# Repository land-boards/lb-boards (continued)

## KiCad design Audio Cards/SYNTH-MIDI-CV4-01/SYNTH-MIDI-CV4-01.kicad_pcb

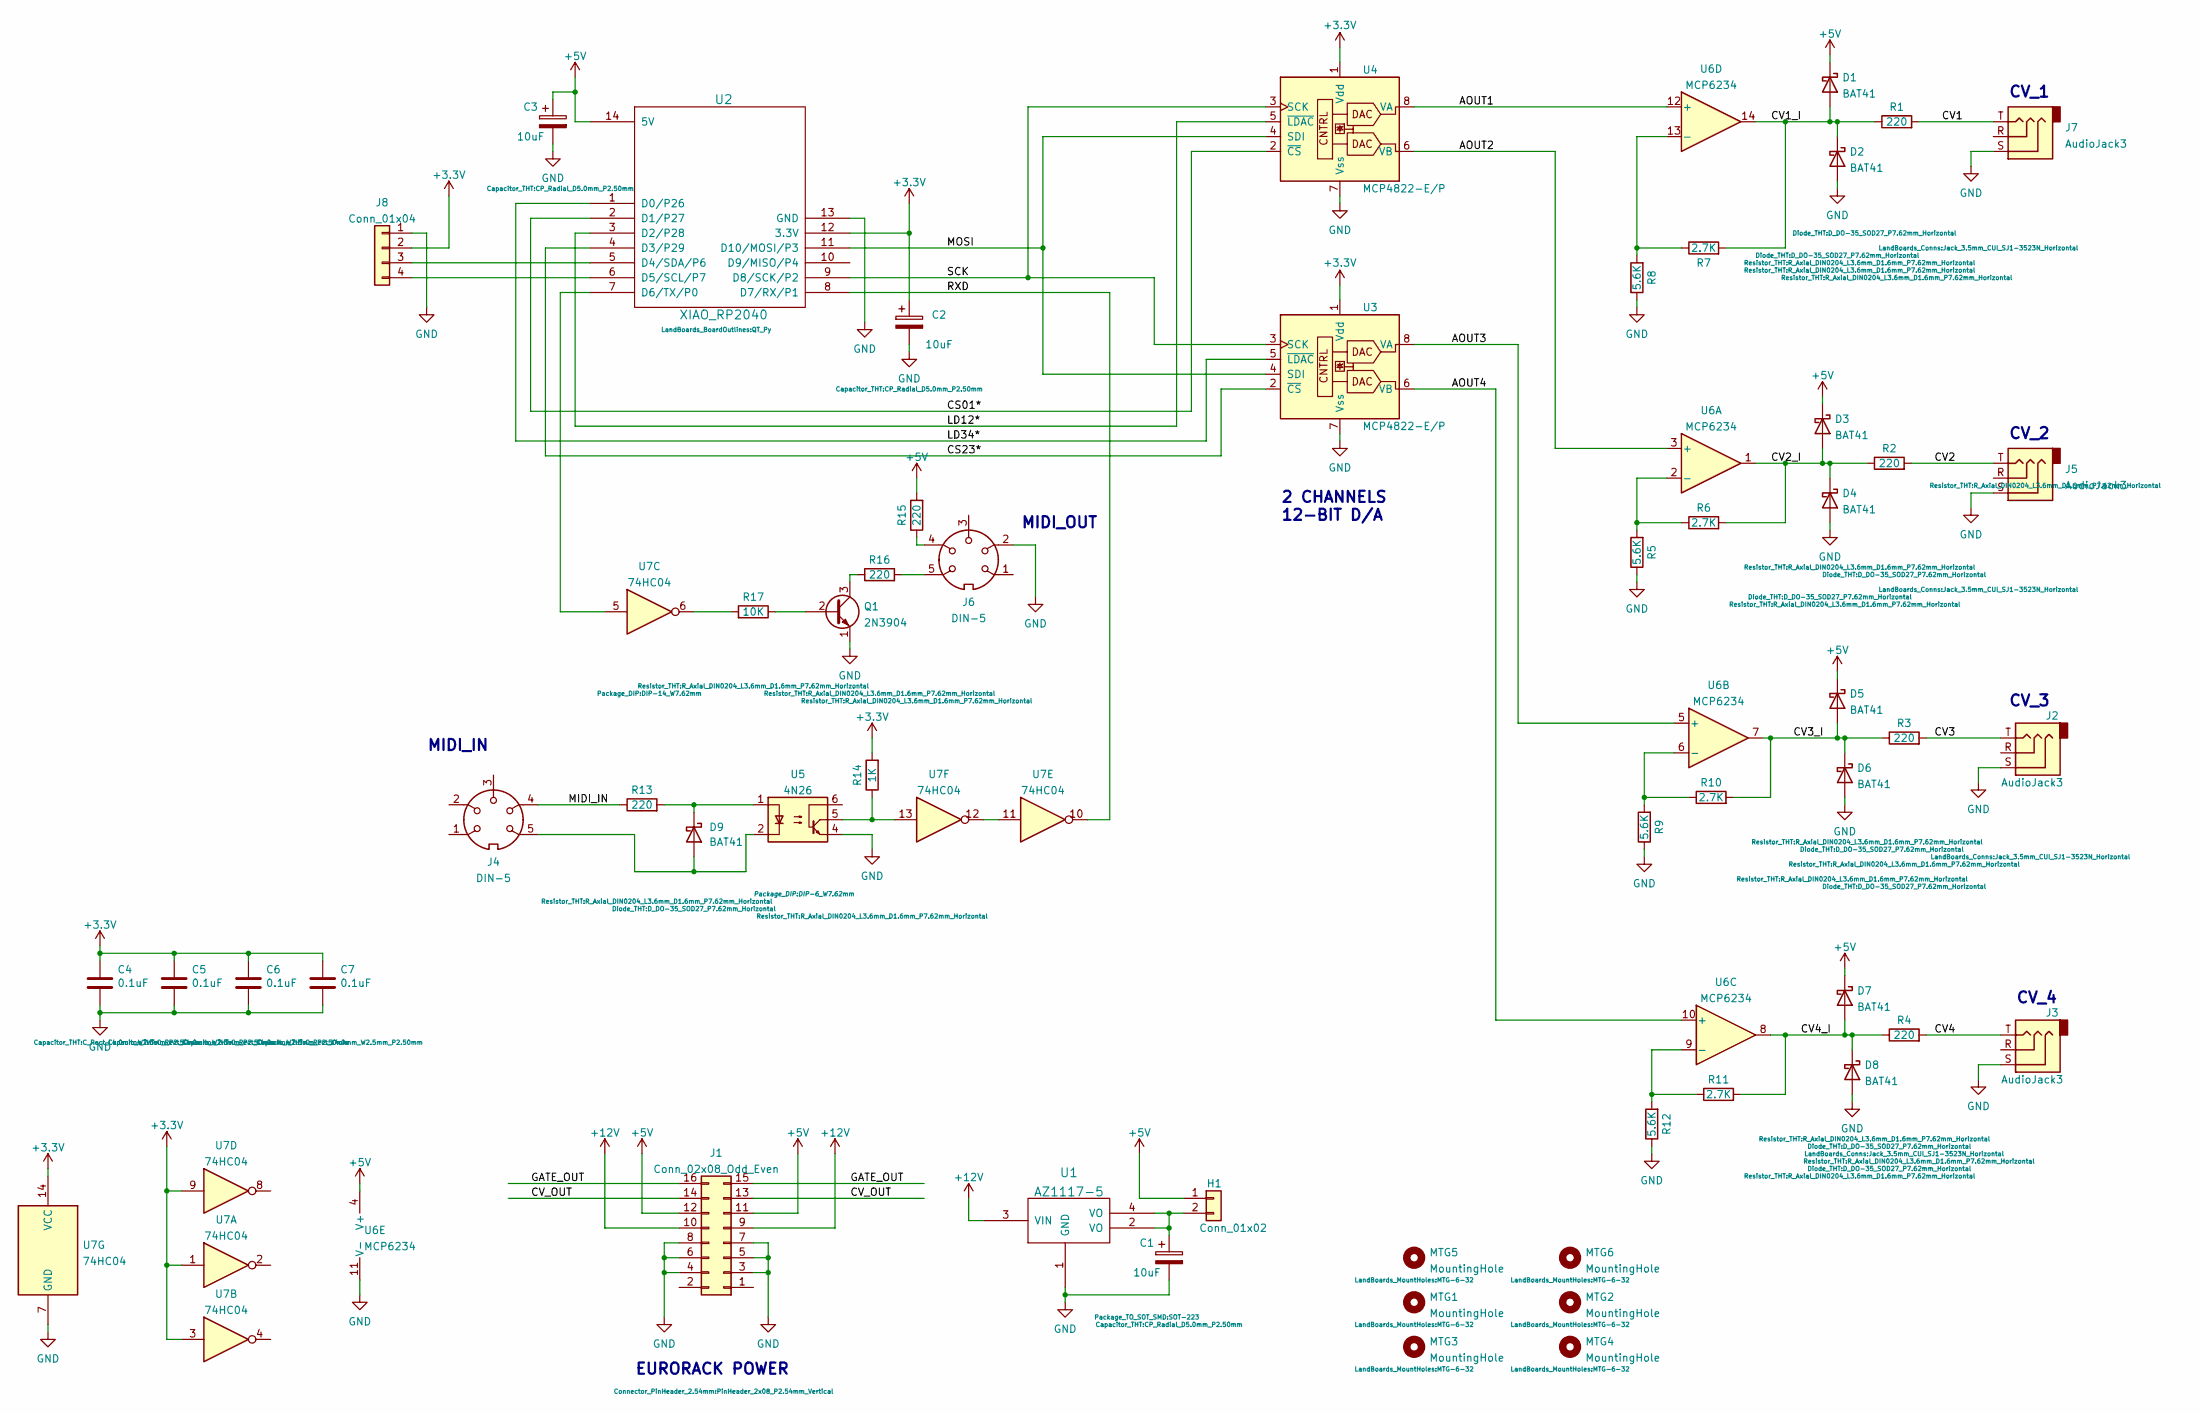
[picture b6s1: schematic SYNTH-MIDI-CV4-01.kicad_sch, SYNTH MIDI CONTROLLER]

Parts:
C1, C2, C3: 10uF; CP_Radial_D5.0mm_P2.50mm
C4, C5, C6, C7: 0.1uF; C_Rect_L4.0mm_W2.5mm_P2.50mm
D1, D2, D3, D4, D5, D6, D7, D8, D9: BAT41; D_DO-35_SOD27_P7.62mm_Horizontal
H1: Conn_01x02; PinHeader_1x02_P2.54mm_Vertical
J1: Conn_02x08_Odd_Even; PinHeader_2x08_P2.54mm_Vertical
J2, J3, J5, J7: AudioJack3; Jack_3.5mm_CUI_SJ1-3523N_Horizontal
J4, J6: DIN-5; MIDI_DIN-5
J8: Conn_01x04
MTG1, MTG2, MTG3, MTG4, MTG5, MTG6: MountingHole; MTG-6-32
Q1: 2N3904; TO-92_Inline
R1, R2, R3, R4, R13, R15, R16: 220; R_Axial_DIN0204_L3.6mm_D1.6mm_P7.62mm_Horizontal
R5, R8, R9, R12: 5.6K; R_Axial_DIN0204_L3.6mm_D1.6mm_P7.62mm_Horizontal
R6, R7, R10, R11: 2.7K; R_Axial_DIN0204_L3.6mm_D1.6mm_P7.62mm_Horizontal
R14: 1K; R_Axial_DIN0204_L3.6mm_D1.6mm_P7.62mm_Horizontal
R17: 10K; R_Axial_DIN0204_L3.6mm_D1.6mm_P7.62mm_Horizontal
U1: AZ1117-5; SOT-223
U2: XIAO_RP2040; QT_Py
U3, U4: MCP4822-E/P; DIP-8_W7.62mm
U5: 4N26; DIP-6_W7.62mm
U6: MCP6234; DIP-14_W7.62mm
U7: 74HC04

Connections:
+3V3: C2.1, C4.1, C5.1, C6.1, C7.1, J8.2, R14.2, U2.12 (3.3V), U3.1 (Vdd), U4.1 (Vdd), U7.1, U7.3, U7.9, U7.14 (VCC)
+5V: C3.1, D1.1 (K), D3.1 (K), D5.1 (K), D7.1 (K), H1.1, J1.11, J1.12, R15.2, U2.14 (5V), U6.4 (V+)
+12V: J1.9, J1.10, U1.3 (VIN)
/AOUT1: U4.8 (VA), U6.12 (+)
/AOUT2: U4.6 (VB), U6.3 (+)
/AOUT3: U3.8 (VA), U6.5 (+)
/AOUT4: U3.6 (VB), U6.10 (+)
/CS01*: U2.2 (D1/P27), U4.2 (~CS)
/CS23*: U2.4 (D3/P29), U3.2 (~CS)
/CV1: J7.T, R1.2
/CV1_I: D1.2 (A), D2.1 (K), R1.1, R7.2, U6.14
/CV2: J5.T, R2.2
/CV2_I: D3.2 (A), D4.1 (K), R2.1, R6.2, U6.1
/CV3: J2.T, R3.2
/CV3_I: D5.2 (A), D6.1 (K), R3.1, R10.2, U6.7
/CV4: J3.T, R4.2
/CV4_I: D7.2 (A), D8.1 (K), R4.1, R11.2, U6.8
/CV_OUT: J1.13, J1.14
/GATE_OUT: J1.15, J1.16
/LD12*: U2.3 (D2/P28), U4.5 (~LDAC)
/LD34*: U2.1 (D0/P26), U3.5 (~LDAC)
/MIDI_IN: J4.4, R13.1
/MOSI: U2.11 (D10/MOSI/P3), U3.4 (SDI), U4.4 (SDI)
/RXD: U2.8 (D7/RX/P1), U7.10
/SCK: U2.9 (D8/SCK/P2), U3.3 (SCK), U4.3 (SCK)
GND: C1.2, C2.2, C3.2, C4.2, C5.2, C6.2, C7.2, D2.2 (A), D4.2 (A), D6.2 (A), D8.2 (A), J1.3, J1.4, J1.5, J1.6, J1.7, J1.8, J2.S, J3.S, J5.S, J6.2, J7.S, J8.1, Q1.1 (E), R5.1, R8.1, R9.1, R12.1, U1.1 (GND), U2.13 (GND), U3.7 (Vss), U4.7 (Vss), U5.4, U6.11 (V-), U7.7 (GND)
unnamed: C1.1, H1.2, U1.2 (VO), U1.4 (VO)
unnamed: D9.1 (K), R13.2, U5.1
unnamed: D9.2 (A), J4.5, U5.2
unnamed: J6.4, R15.1
unnamed: J6.5, R16.2
unnamed: J8.3, U2.5 (D4/SDA/P6)
unnamed: J8.4, U2.6 (D5/SCL/P7)
unnamed: Q1.2 (B), R17.1
unnamed: Q1.3 (C), R16.1
unnamed: R5.2, R6.1, U6.2 (-)
unnamed: R7.1, R8.2, U6.13 (-)
unnamed: R9.2, R10.1, U6.6 (-)
unnamed: R11.1, R12.2, U6.9 (-)
unnamed: R14.1, U5.5, U7.13
unnamed: R17.2, U7.6
unnamed: U2.7 (D6/TX/P0), U7.5
unnamed: U7.11, U7.12

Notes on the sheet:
CV_1
CV_3
MIDI_IN
2 CHANNELS 12-BIT D/A
MIDI_OUT
CV_4
CV_2
EURORACK POWER

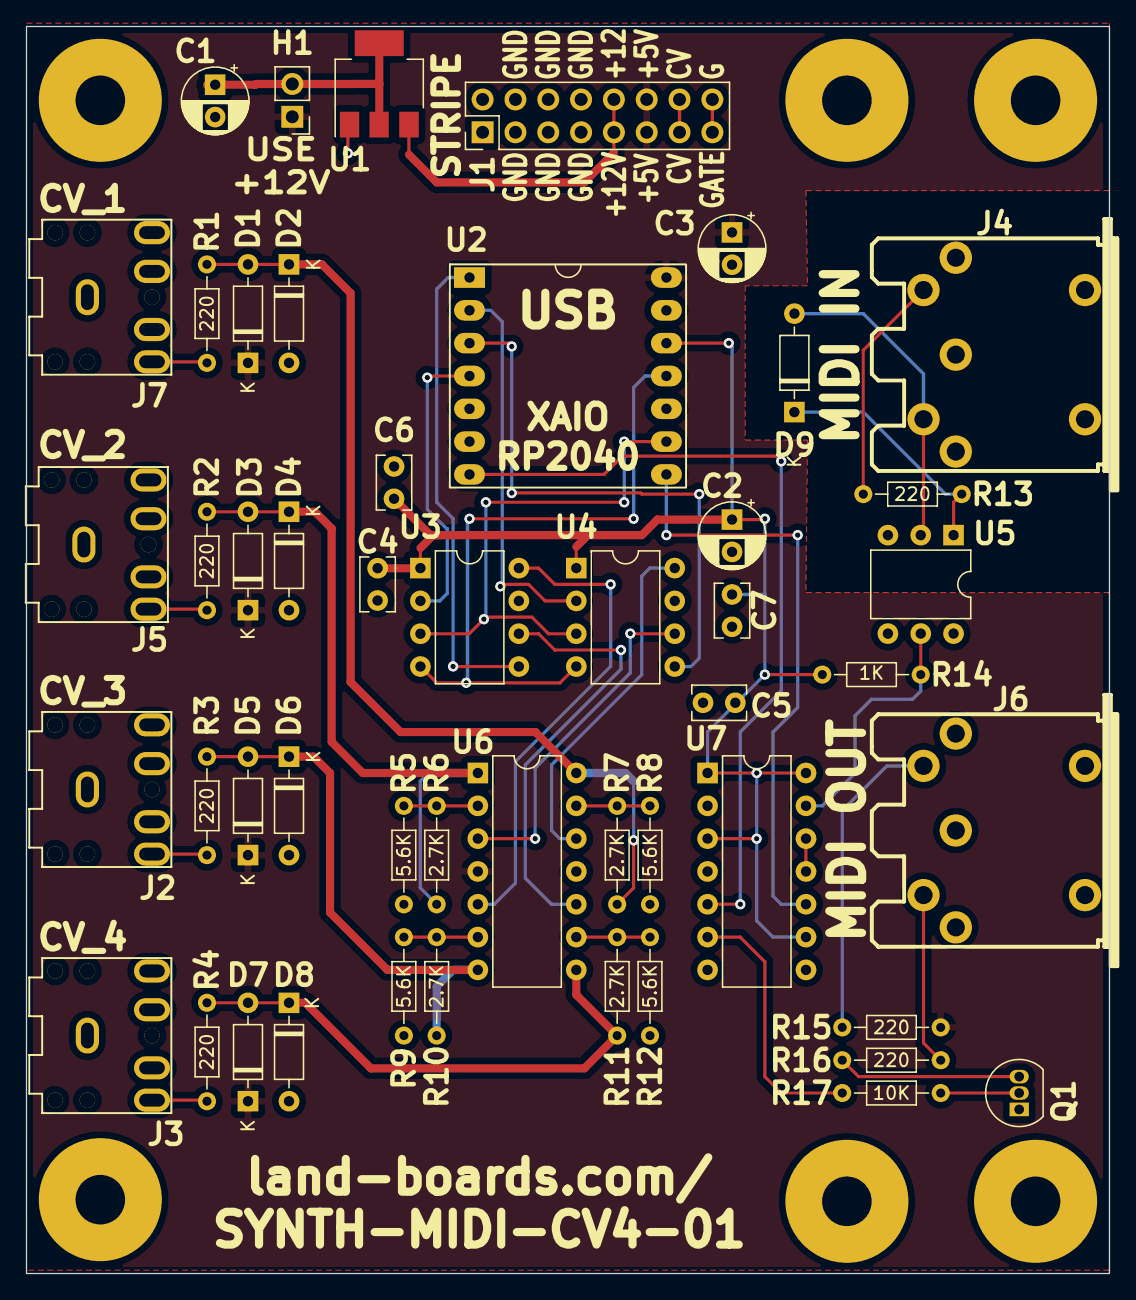
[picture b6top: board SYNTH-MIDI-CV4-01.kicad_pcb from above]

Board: 2 copper layers, 83.8 x 96.5 mm, 55 parts (0 on the bottom side), 41 nets.

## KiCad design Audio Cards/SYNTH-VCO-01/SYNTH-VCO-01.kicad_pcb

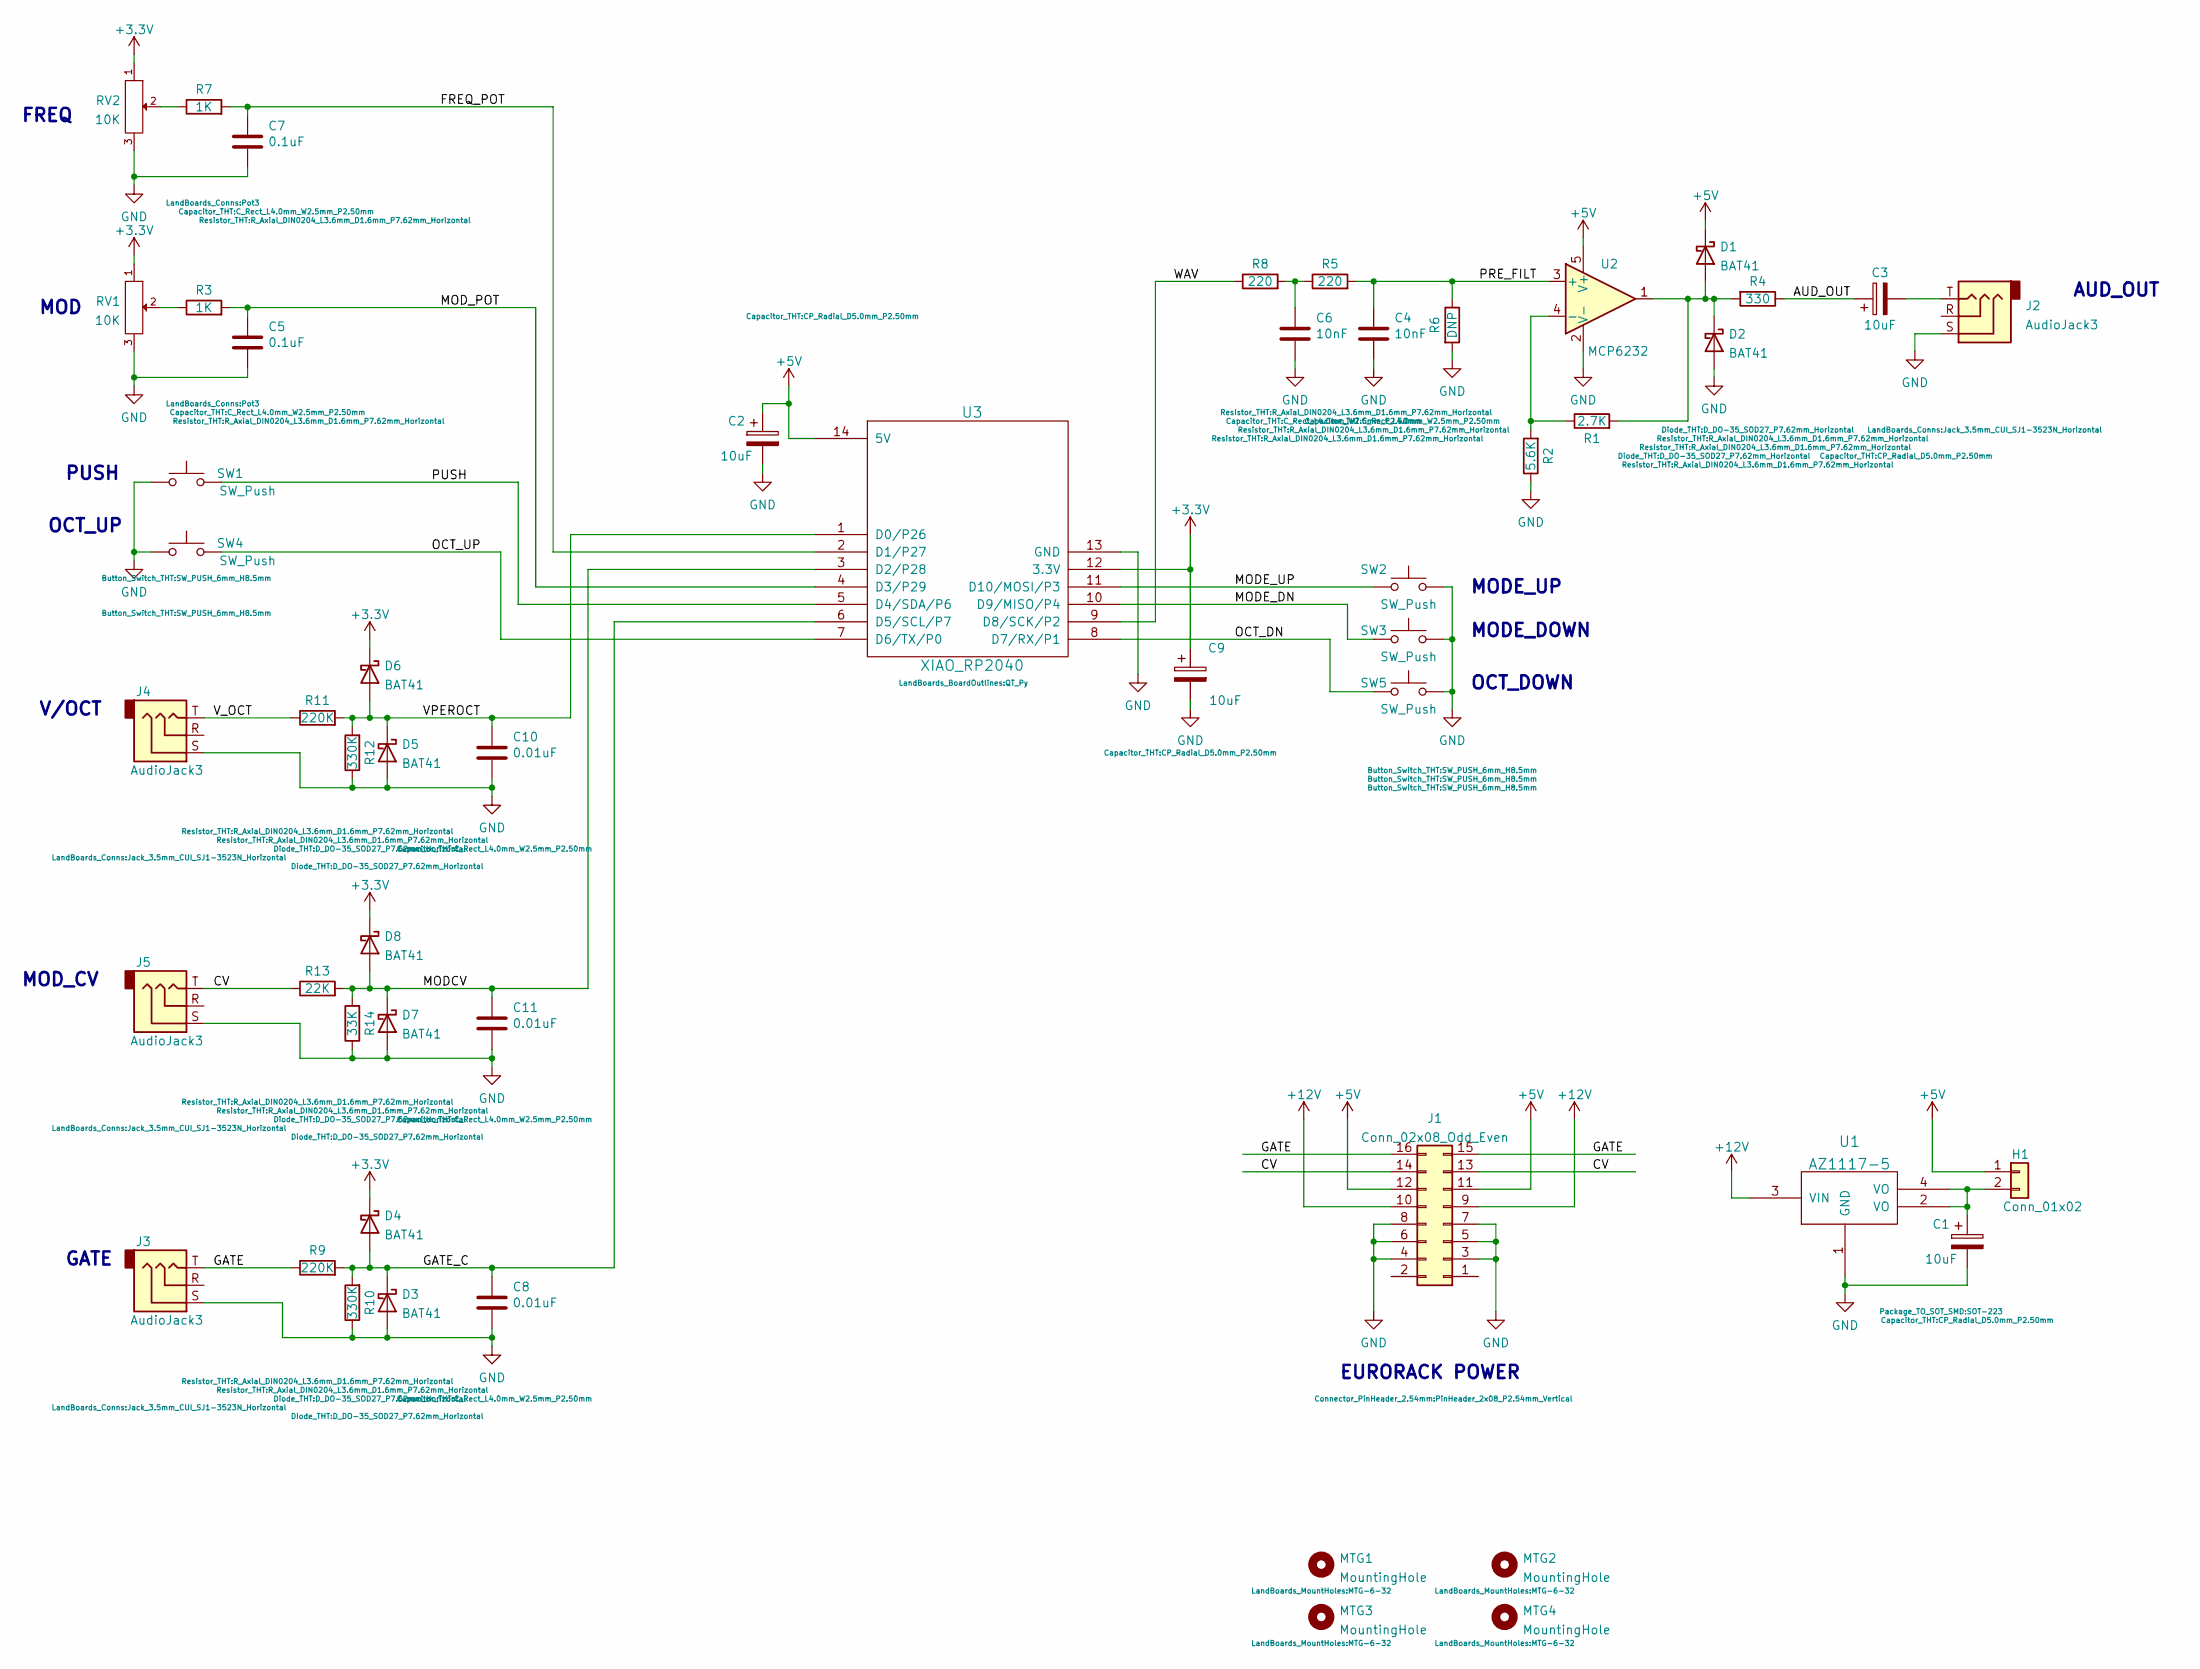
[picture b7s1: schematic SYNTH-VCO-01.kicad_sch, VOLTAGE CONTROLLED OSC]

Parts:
C1, C2, C3, C9: 10uF; CP_Radial_D5.0mm_P2.50mm
C4, C6: 10nF; C_Rect_L4.0mm_W2.5mm_P2.50mm
C5, C7: 0.1uF; C_Rect_L4.0mm_W2.5mm_P2.50mm
C8, C10, C11: 0.01uF; C_Rect_L4.0mm_W2.5mm_P2.50mm
D1, D2, D3, D4, D5, D6, D7, D8: BAT41; D_DO-35_SOD27_P7.62mm_Horizontal
H1: Conn_01x02; PinHeader_1x02_P2.54mm_Vertical
J1: Conn_02x08_Odd_Even; PinHeader_2x08_P2.54mm_Vertical
J2, J3, J4, J5: AudioJack3; Jack_3.5mm_CUI_SJ1-3523N_Horizontal
MTG1, MTG2, MTG3, MTG4: MountingHole; MTG-6-32
R1: 2.7K; R_Axial_DIN0204_L3.6mm_D1.6mm_P7.62mm_Horizontal
R2: 5.6K; R_Axial_DIN0204_L3.6mm_D1.6mm_P7.62mm_Horizontal
R3, R7: 1K; R_Axial_DIN0204_L3.6mm_D1.6mm_P7.62mm_Horizontal
R4: 330; R_Axial_DIN0204_L3.6mm_D1.6mm_P7.62mm_Horizontal
R5, R8: 220; R_Axial_DIN0204_L3.6mm_D1.6mm_P7.62mm_Horizontal
R6: DNP; R_Axial_DIN0204_L3.6mm_D1.6mm_P7.62mm_Horizontal
R9, R11: 220K; R_Axial_DIN0204_L3.6mm_D1.6mm_P7.62mm_Horizontal
R10, R12: 330K; R_Axial_DIN0204_L3.6mm_D1.6mm_P7.62mm_Horizontal
R13: 22K; R_Axial_DIN0204_L3.6mm_D1.6mm_P7.62mm_Horizontal
R14: 33K; R_Axial_DIN0204_L3.6mm_D1.6mm_P7.62mm_Horizontal
RV1, RV2: 10K; Pot3
SW1, SW2, SW3, SW4, SW5: SW_Push; SW_PUSH_6mm_H8.5mm
U1: AZ1117-5; SOT-223
U2: MCP6232; DIP-8_W7.62mm
U3: XIAO_RP2040; QT_Py

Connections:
+3V3: C9.1, D4.1 (K), D6.1 (K), D8.1 (K), RV1.1, RV2.1, U3.12 (3.3V)
+5V: C2.1, D1.1 (K), H1.1, J1.11, J1.12, U2.5 (V+), U3.14 (5V)
+12V: J1.9, J1.10, U1.3 (VIN)
/AUD_OUT: C3.1, R4.1
/CV: J1.13, J1.14, J5.T, R13.1
/FREQ_POT: C7.1, R7.2, U3.2 (D1/P27)
/GATE: J1.15, J1.16, J3.T, R9.1
/GATE_C: C8.1, D3.1 (K), D4.2 (A), R9.2, R10.2, U3.6 (D5/SCL/P7)
/MODCV: C11.1, D7.1 (K), D8.2 (A), R13.2, R14.2, U3.3 (D2/P28)
/MODE_DN: SW3.1, U3.10 (D9/MISO/P4)
/MODE_UP: SW2.1, U3.11 (D10/MOSI/P3)
/MOD_POT: C5.1, R3.2, U3.4 (D3/P29)
/OCT_DN: SW5.1, U3.8 (D7/RX/P1)
/OCT_UP: SW4.2, U3.7 (D6/TX/P0)
/PRE_FILT: C4.1, R5.2, R6.1, U2.3 (+)
/PUSH: SW1.2, U3.5 (D4/SDA/P6)
/VPEROCT: C10.1, D5.1 (K), D6.2 (A), R11.2, R12.2, U3.1 (D0/P26)
/V_OCT: J4.T, R11.1
/WAV: R8.1, U3.9 (D8/SCK/P2)
GND: C1.2, C2.2, C4.2, C5.2, C6.2, C7.2, C8.2, C9.2, C10.2, C11.2, D2.2 (A), D3.2 (A), D5.2 (A), D7.2 (A), J1.3, J1.4, J1.5, J1.6, J1.7, J1.8, J2.S, J3.S, J4.S, J5.S, R2.1, R6.2, R10.1, R12.1, R14.1, RV1.3, RV2.3, SW1.1, SW2.2, SW3.2, SW4.1, SW5.2, U1.1 (GND), U2.2 (V-), U3.13 (GND)
unnamed: C1.1, H1.2, U1.2 (VO), U1.4 (VO)
unnamed: C3.2, J2.T
unnamed: C6.1, R5.1, R8.2
unnamed: D1.2 (A), D2.1 (K), R1.2, R4.2, U2.1
unnamed: R1.1, R2.2, U2.4 (-)
unnamed: R3.1, RV1.2
unnamed: R7.1, RV2.2

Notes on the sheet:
OCT_UP
AUD_OUT
GATE
V/OCT
MODE_DOWN
MOD_CV
FREQ
OCT_DOWN
MODE_UP
PUSH
MOD
EURORACK POWER

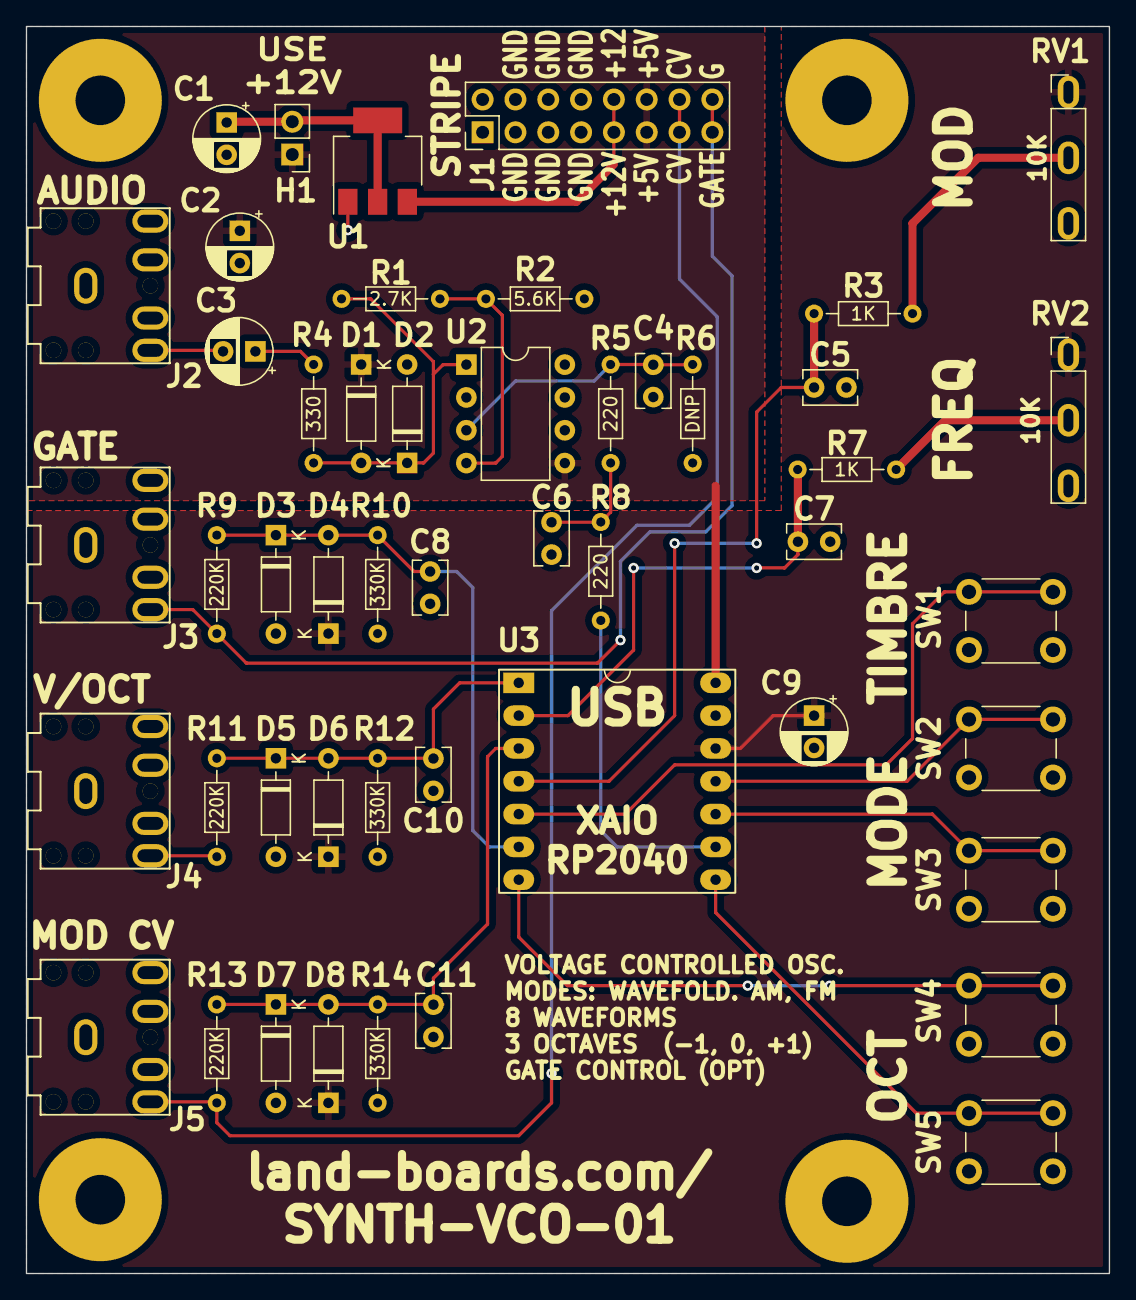
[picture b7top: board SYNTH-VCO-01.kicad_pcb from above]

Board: 2 copper layers, 83.8 x 96.5 mm, 53 parts (0 on the bottom side), 27 nets.
